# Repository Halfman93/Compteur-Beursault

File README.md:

# Compteur-Beursault
Système de comptage de point pour un jeu d'arc

Le système est fonctionnel. Il est basé sur des arduino nano pour des raisons de cout, les cartes acheté sur ebay coutant moins chers que les composants individuellement. 

Les PCB réalisés peuvent etre repris/Modifié à volonté. Au besoin ils peuvent etre commandé directement sur ce site : https://dirtypcbs.com/store/designer/browse/5639
Attention, en cas de livraison UPS des frais de douanes seront ajoutés. 

Le compteur est nommé scoreur.
Les 2 autres cartes à savoir télécommande et recepteur sont pour la partie radio. 

Une télécommande sans fil avec un recepteur (en 433MHz) est en cours de test. Les schématiques et logiciels sont déjà disponible. La documentation complète sera terminée lorsque le système sera qualifié. 

Have fun !

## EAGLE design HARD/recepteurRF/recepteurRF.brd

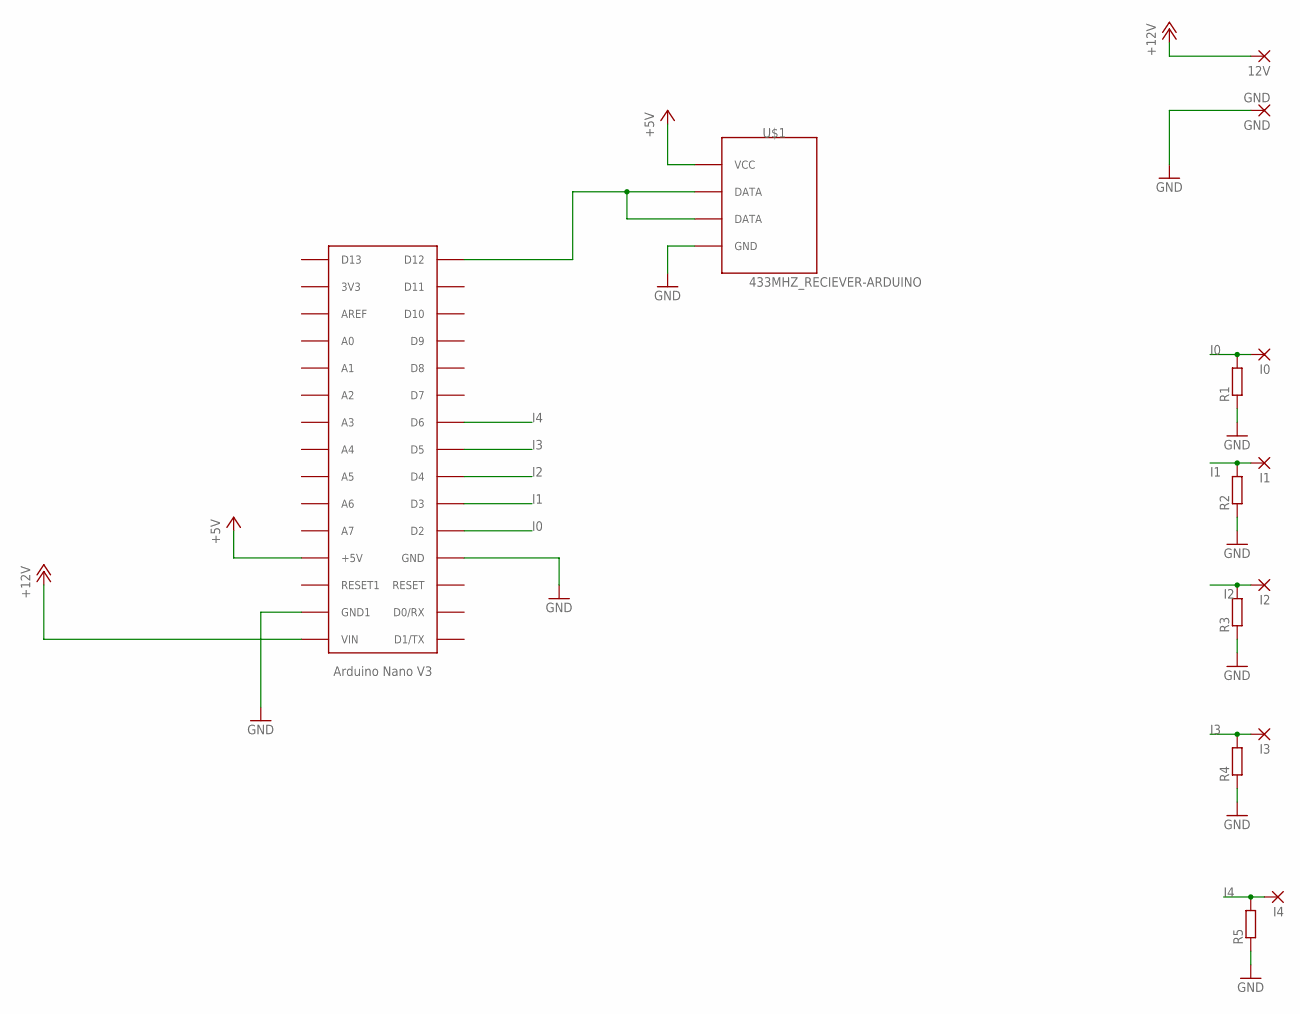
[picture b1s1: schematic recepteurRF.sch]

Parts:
12V: SMD5; SMD2,54-5,08
GND: GND; SMD2,54-5,08
I0, I1, I2, I3, I4: SMD5; SMD2,54-5,08
R1, R2, R3, R4, R5: R-EU_R1206; R1206
U$1: 433MHZ_RECIEVER-ARDUINO
U$2: ARDUINONANO; PDIP-32

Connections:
+5V: U$1.VCC, U$2.+5V
+12V: 12V.1, U$2.VIN
GND: GND.1, R1.1, R2.1, R3.1, R4.1, R5.1, U$1.GND, U$2.GND, U$2.GND1
I0: I0.1, R1.2, U$2.D2
I1: I1.1, R2.2, U$2.D3
I2: I2.1, R3.2, U$2.D4
I3: I3.1, R4.2, U$2.D5
I4: I4.1, R5.2, U$2.D6
unnamed: U$1.DATA@0 (DATA), U$1.DATA@1 (DATA), U$2.D12

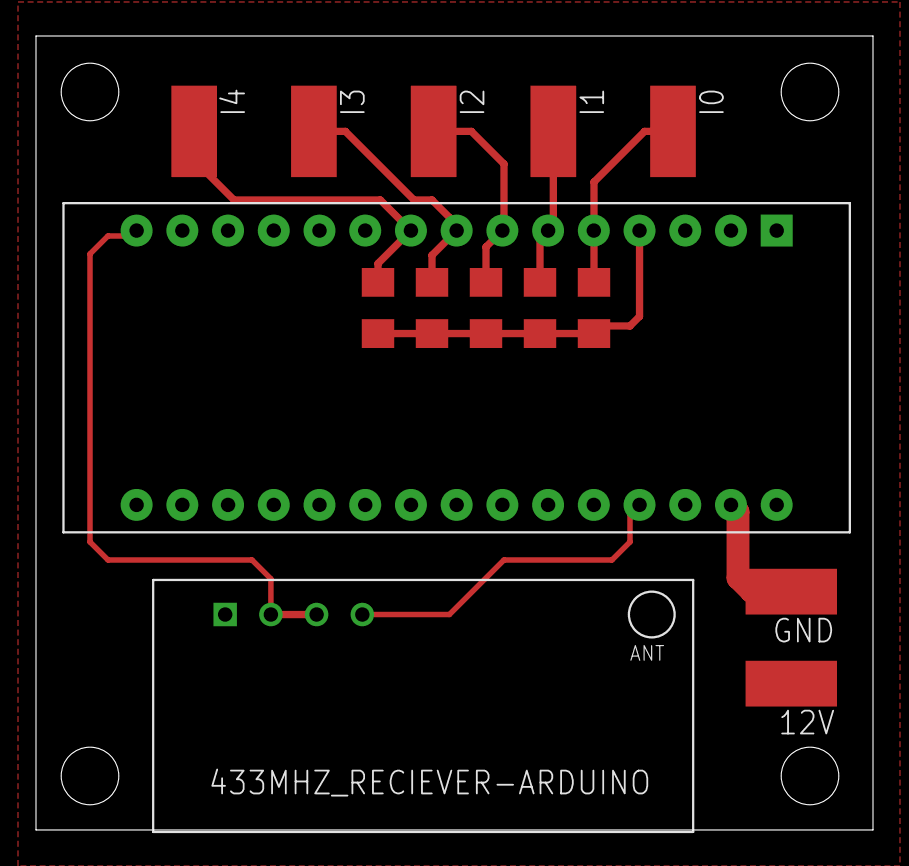
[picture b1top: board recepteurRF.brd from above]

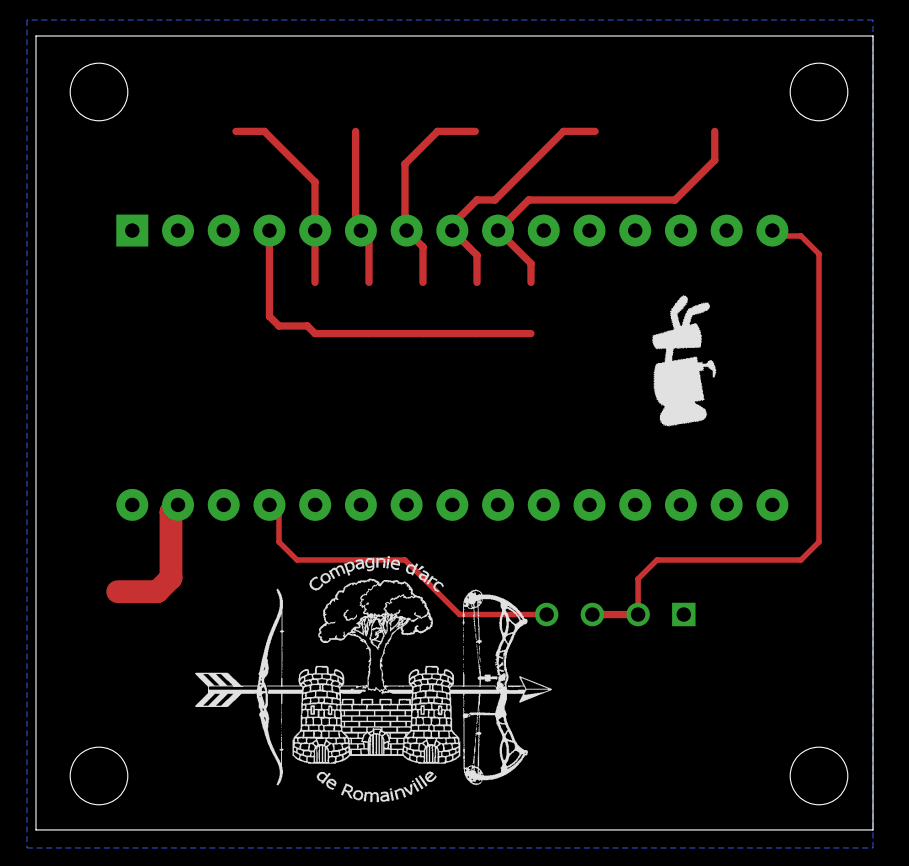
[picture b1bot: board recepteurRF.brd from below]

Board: 2 copper layers, 46.5 x 44.1 mm, 16 parts (2 on the bottom side), 9 nets.

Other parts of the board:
U$3: LOGO
U$4: LOGO_GROS

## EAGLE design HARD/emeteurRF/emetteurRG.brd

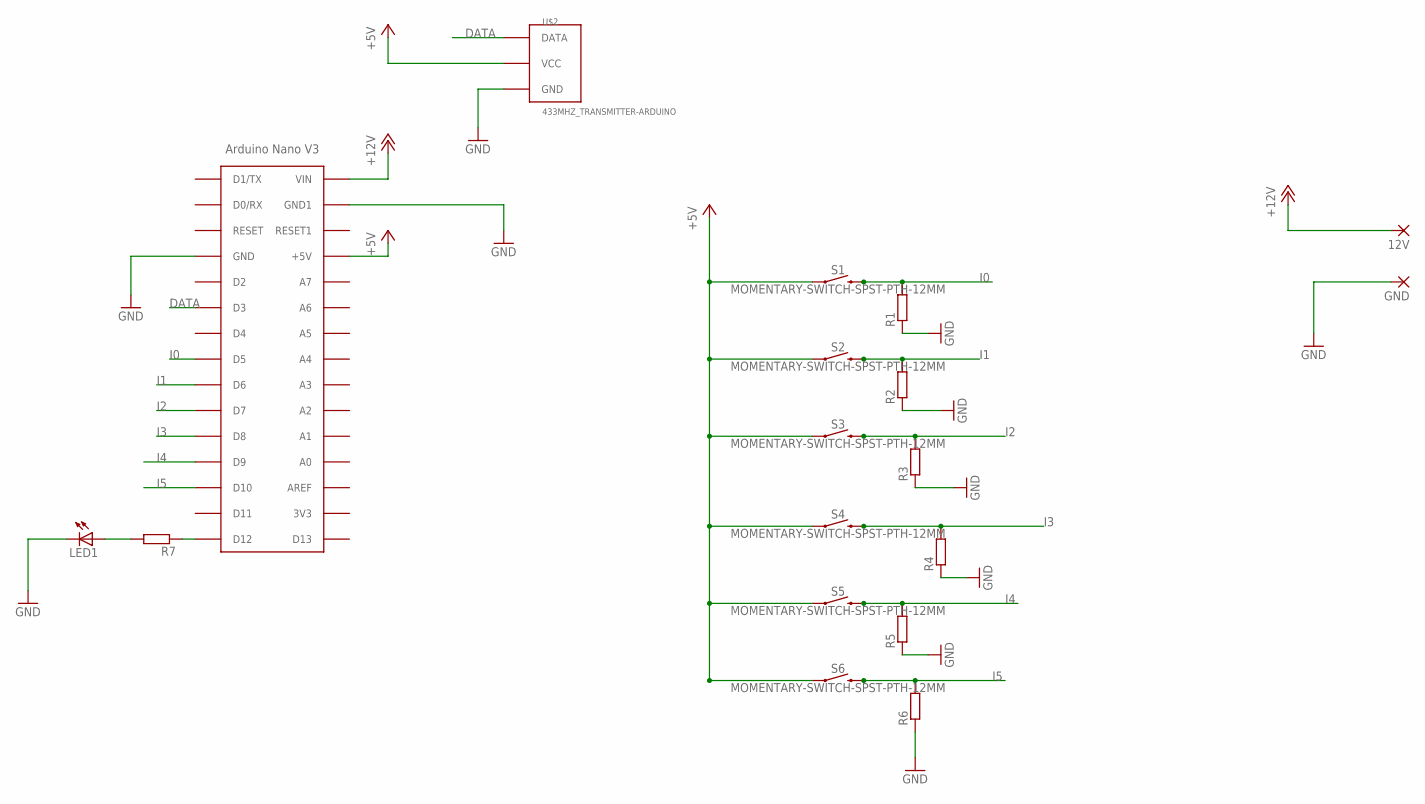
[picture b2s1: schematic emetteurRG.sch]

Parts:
12V: SMD5; SMD2,54-5,08
GND: SMD5; SMD2,54-5,08
LED1: LED5MM
R1, R2, R3, R4, R5, R6, R7: R-EU_R1206; R1206
S1, S2, S3, S4, S5, S6: MOMENTARY-SWITCH-SPST-PTH-12MM; TACTILE_SWITCH_PTH_12MM
U$1: ARDUINONANO; PDIP-32
U$2: 433MHZ_TRANSMITTER-ARDUINO

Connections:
+5V: S1.1, S2.1, S3.1, S4.1, S5.1, S6.1, U$1.+5V, U$2.VCC
+12V: 12V.1, U$1.VIN
DATA: U$1.D3, U$2.DATA
GND: GND.1, LED1.K (C), R1.1, R2.1, R3.1, R4.1, R5.1, R6.1, U$1.GND, U$1.GND1, U$2.GND
I0: R1.2, S1.3 (2), U$1.D5
I1: R2.2, S2.3 (2), U$1.D6
I2: R3.2, S3.3 (2), U$1.D7
I3: R4.2, S4.3 (2), U$1.D8
I4: R5.2, S5.3 (2), U$1.D9
I5: R6.2, S6.3 (2), U$1.D10
unnamed: LED1.A, R7.2
unnamed: R7.1, U$1.D12

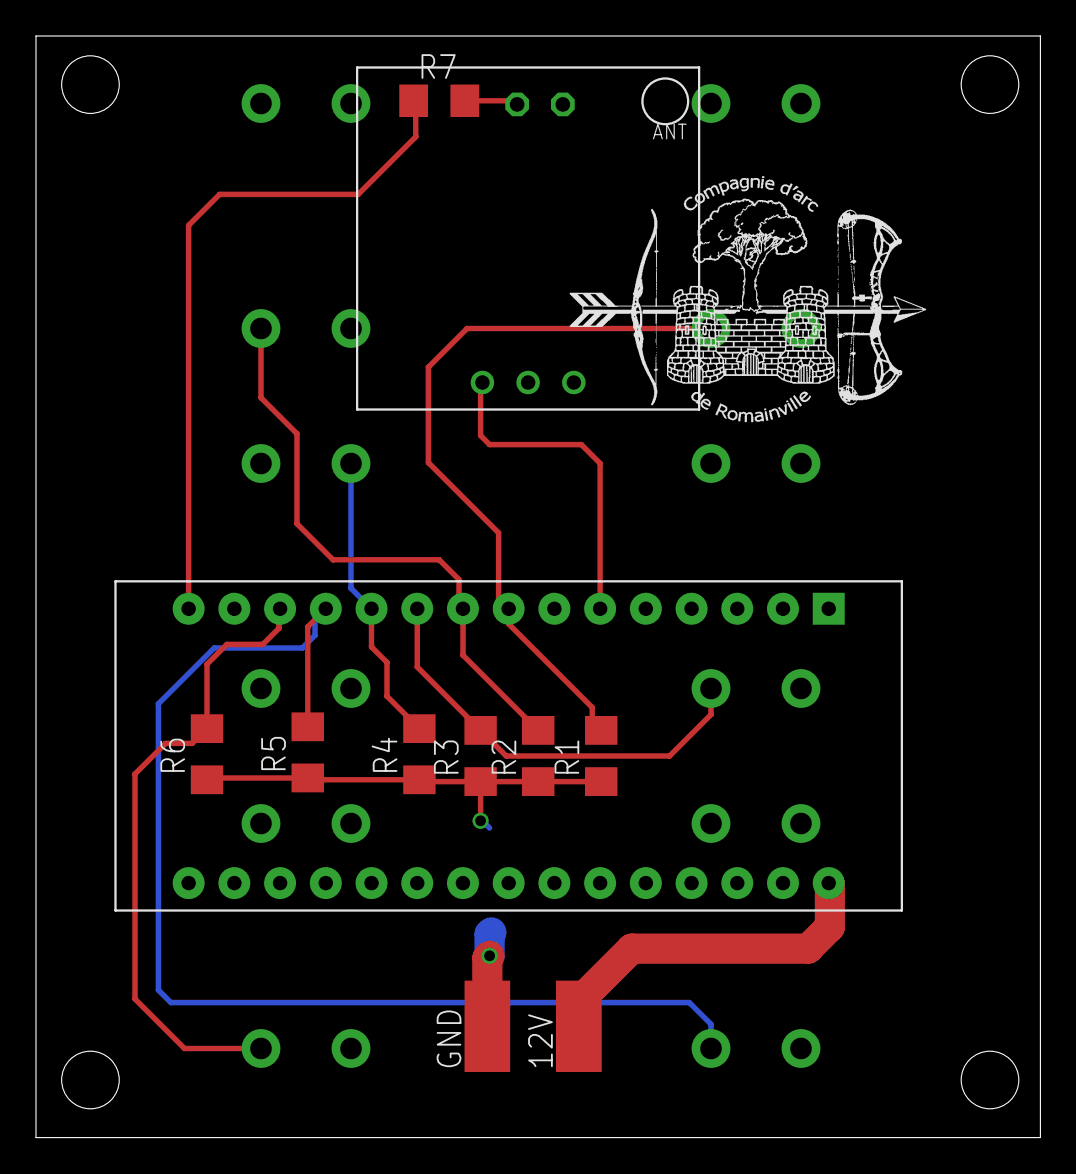
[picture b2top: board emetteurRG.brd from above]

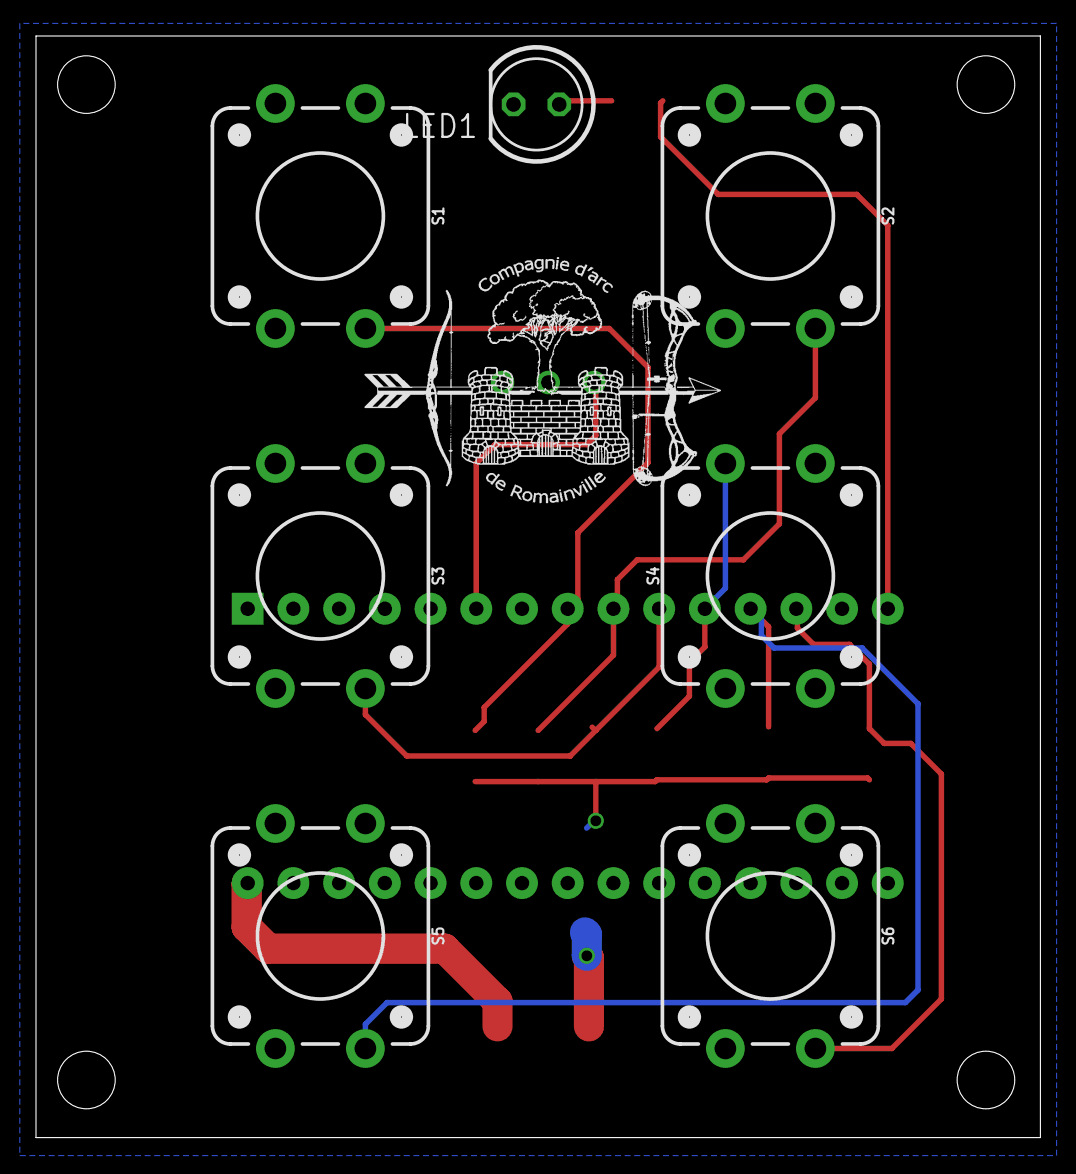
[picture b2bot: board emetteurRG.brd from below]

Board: 2 copper layers, 55.8 x 61.2 mm, 20 parts (8 on the bottom side), 12 nets.

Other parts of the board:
U$3, U$4: LOGO

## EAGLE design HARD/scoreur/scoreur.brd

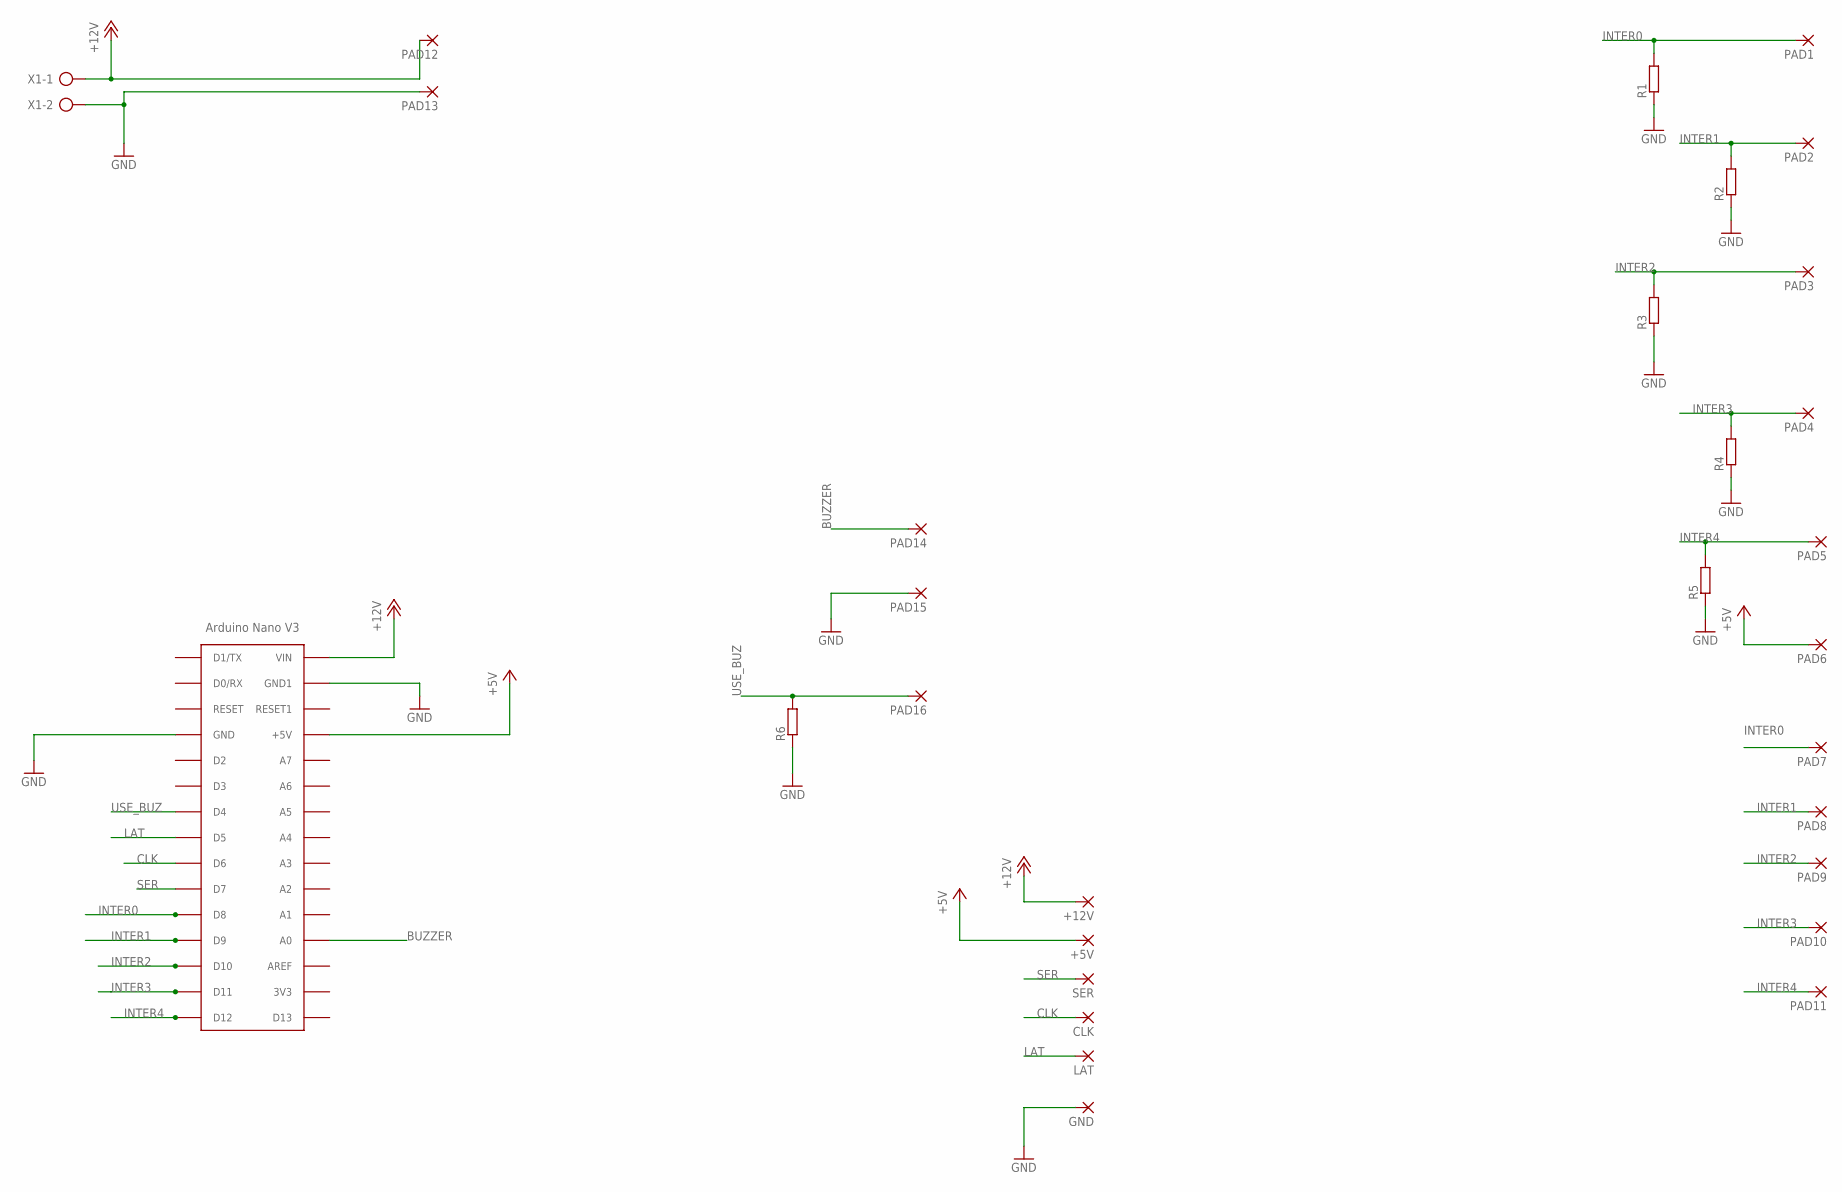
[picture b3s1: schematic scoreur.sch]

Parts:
+5V, +12V: SMD5; SMD2,54-5,08
CLK: SMD5; SMD2,54-5,08
GND: SMD5; SMD2,54-5,08
LAT: SMD5; SMD2,54-5,08
PAD1, PAD2, PAD3, PAD4, PAD5, PAD6, PAD7, PAD8, PAD9, PAD10, PAD11, PAD12, PAD13, PAD14, PAD15, PAD16: SMD5; SMD2,54-5,08
R1, R2, R3, R4, R5, R6: R-EU_R1206; R1206
SER: SMD5; SMD2,54-5,08
U$1: ARDUINONANO; PDIP-32
X1: AK500/2-H

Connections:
+5V: +5V.1, PAD6.1, U$1.+5V
+12V: +12V.1, PAD12.1, U$1.VIN, X1.1
BUZZER: PAD14.1, U$1.A7 (A0)
CLK: CLK.1, U$1.D6
GND: GND.1, PAD13.1, PAD15.1, R1.1, R2.1, R3.1, R4.1, R5.1, R6.1, U$1.GND, U$1.GND1, X1.2
INTER0: PAD1.1, PAD7.1, R1.2, U$1.D8
INTER1: PAD2.1, PAD8.1, R2.2, U$1.D9
INTER2: PAD3.1, PAD9.1, R3.2, U$1.D10
INTER3: PAD4.1, PAD10.1, R4.2, U$1.D11
INTER4: PAD5.1, PAD11.1, R5.2, U$1.D12
LAT: LAT.1, U$1.D5
SER: SER.1, U$1.D7
USE_BUZ: PAD16.1, R6.2, U$1.D4

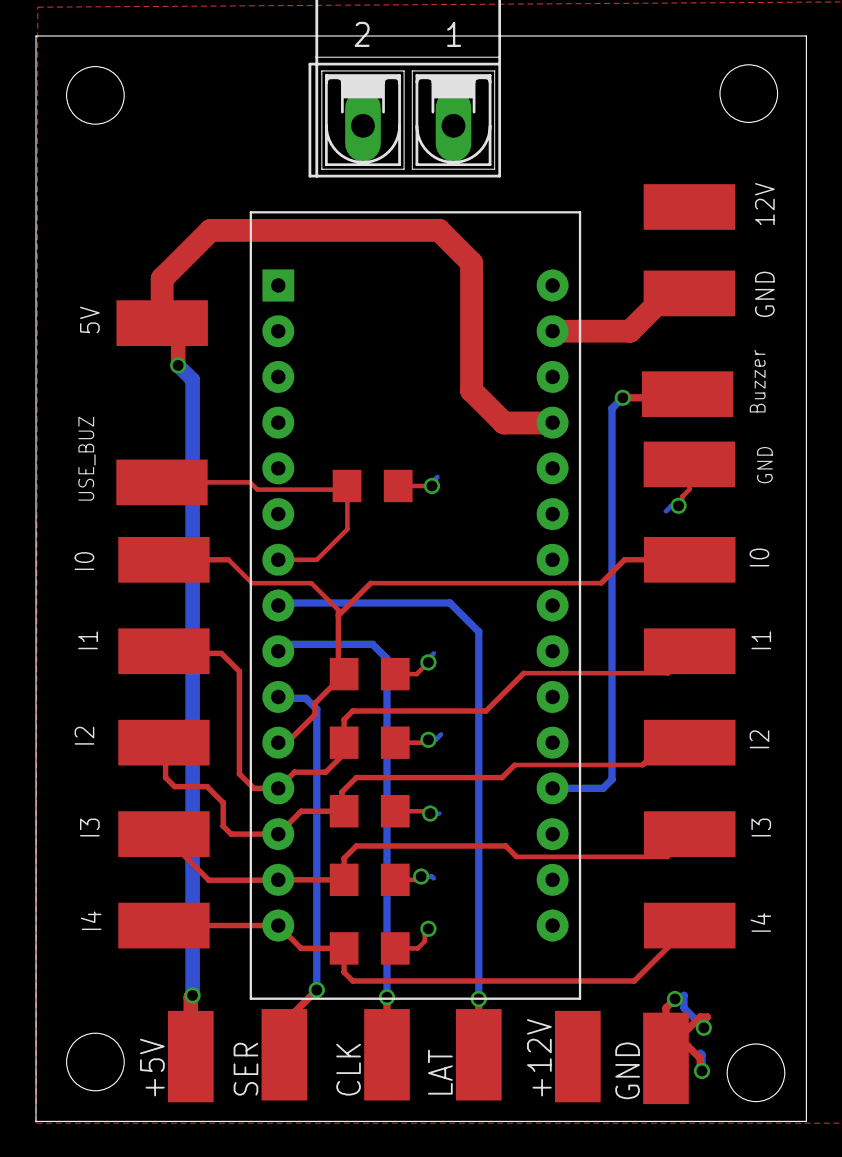
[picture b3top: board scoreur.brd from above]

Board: 2 copper layers, 42.8 x 60.3 mm, 31 parts (1 on the bottom side), 13 nets.

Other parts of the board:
U$2: LOGO

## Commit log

2018-07-27 Premier commit
2018-09-10 Correction bug d'affichage en cas de doute. Affichage d'un tiret en cas de doute au lieu d'un nombre qui clignote. Plus visuel et compatible avec la version sans fil.

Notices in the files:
parts and their libraries:
SparkFun-Switches: Licensing: Creative Commons ShareAlike 4.0 International - https://creativecommons.org/licenses/by-sa/4.0
